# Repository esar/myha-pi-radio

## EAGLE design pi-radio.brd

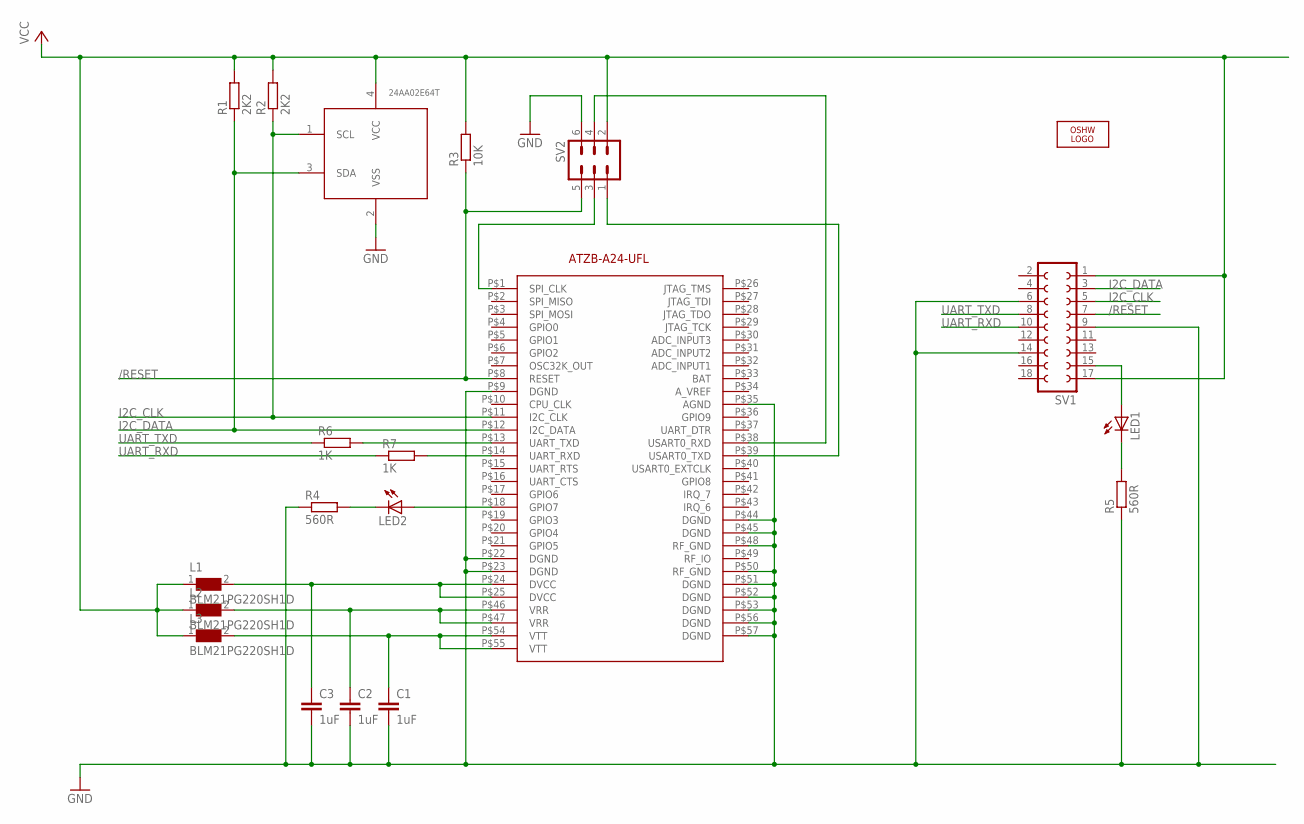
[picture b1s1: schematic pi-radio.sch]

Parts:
C1, C2, C3: 1uF; C0603
L1, L2, L3: BLM21PG220SH1D; 0805
LED1, LED2: LEDSML0805; SML0805
LOGO1: OSHW_LOGO_8MILX0100-NT; OSHW_8X100_NOTEXT
R1, R2: 2K2; R0603
R3: 10K; R0603
R4, R5: 560R; R0603
R6, R7: 1K; R0603
SV1: FE09-2
SV2: MA03-2
U$1: ATZB-A24-UFL
U$2: 24AA02E64T; SOT23-5L

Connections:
/RESET: R3.1, SV1.7, SV2.5, U$1.P$8 (RESET)
GND: C1.2, C2.2, C3.2, R4.1, R5.1, SV1.6, SV1.9, SV1.14, SV2.6, U$1.P$9 (DGND), U$1.P$22 (DGND), U$1.P$23 (DGND), U$1.P$35 (AGND), U$1.P$44 (DGND), U$1.P$45 (DGND), U$1.P$48 (RF_GND), U$1.P$50 (RF_GND), U$1.P$51 (DGND), U$1.P$52 (DGND), U$1.P$53 (DGND), U$1.P$56 (DGND), U$1.P$57 (DGND), U$2.2 (VSS)
I2C_CLK: R2.1, SV1.5, U$1.P$11 (I2C_CLK), U$2.1 (SCL)
I2C_DATA: R1.1, SV1.3, U$1.P$12 (I2C_DATA), U$2.3 (SDA)
unnamed: LED1.A, SV1.15
unnamed: LED2.A, U$1.P$18 (GPIO7)
unnamed: C1.1, L3.2, U$1.P$54 (VTT), U$1.P$55 (VTT)
unnamed: C2.1, L2.2, U$1.P$46 (VRR), U$1.P$47 (VRR)
unnamed: C3.1, L1.2, U$1.P$24 (DVCC), U$1.P$25 (DVCC)
unnamed: LED2.C, R4.2
unnamed: LED1.C, R5.2
unnamed: SV2.1, U$1.P$39 (USART0_TXD)
unnamed: SV2.4, U$1.P$38 (USART0_RXD)
unnamed: R7.2, U$1.P$14 (UART_RXD)
unnamed: R6.2, U$1.P$13 (UART_TXD)
SPI_CLK: SV2.3, U$1.P$1 (SPI_CLK)
UART_RXD: R7.1, SV1.10
UART_TXD: R6.1, SV1.8
VCC: L1.1, L2.1, L3.1, R1.2, R2.2, R3.2, SV1.1, SV1.17, SV2.2, U$2.4 (VCC)

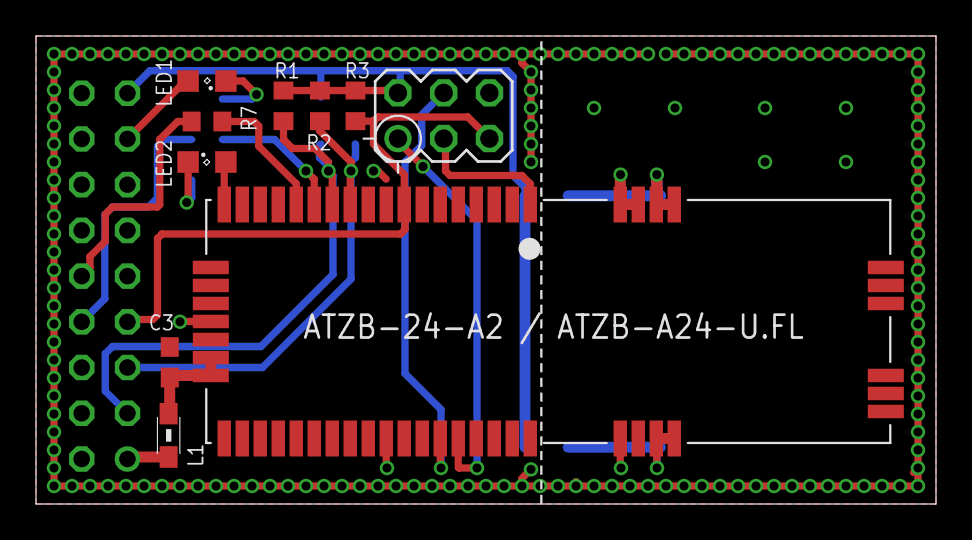
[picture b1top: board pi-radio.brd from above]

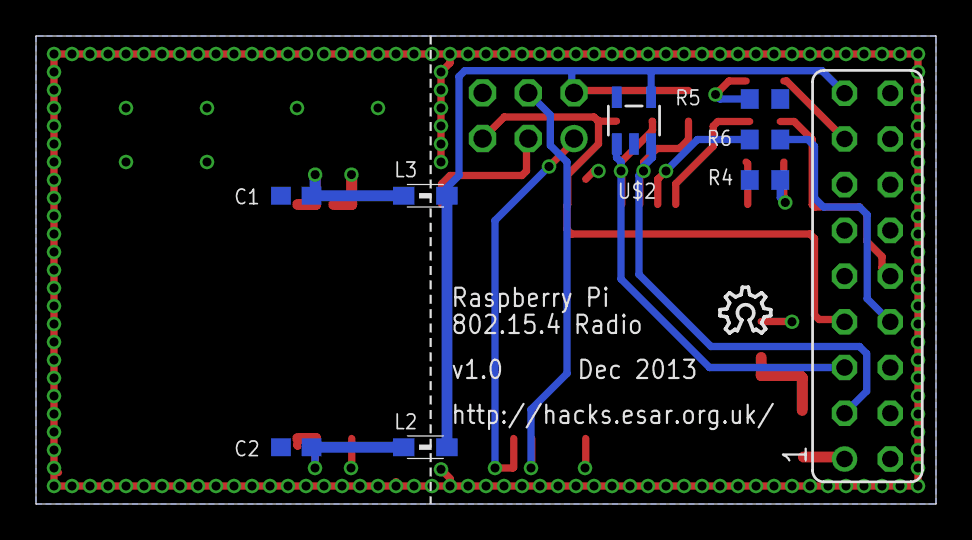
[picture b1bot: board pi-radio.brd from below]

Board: 2 copper layers, 50.0 x 26.0 mm, 20 parts (10 on the bottom side), 19 nets.

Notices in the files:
parts and their libraries:
EagleLibrary_Wuerth_Elektronik_eiSos_Ver: Copyright: Würth Elektronik
